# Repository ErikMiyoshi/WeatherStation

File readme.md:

# 💡 Multi-Domain Learning Project: Hardware, Firmware & Software

Welcome to this project that combines **hardware design**, **embedded firmware**, and **application-level software**. The project is a portable weather station that gets temperature, humidity, pressure and show on a dashboard.

## 🧭 Project Goal

This is a personal project for me to learning all aspects of an embedded system project that involves:

- 🔧 **Hardware**: Circuit design, schematics, and PCB development
- 🧠 **Firmware**: Embedded code for microcontrollers, in this case ESP32
- 💻 **Software**: Applications that interact with the device, including dashboards and data logging

The objective is to **understand how these layers connect**, and how to manage a multidisciplinary project effectively.

---

## 🗂 Repository Structure

WeatherStation/
├── HW/ # Schematics, PCB design files (KiCad, etc.)
├── FW/ # Embedded C/C++ code (e.g., ESP-IDF)
├── SW/ # Python, Flask, GUI application (e.g., dashboard)
├── docs/ # Documentation, diagrams, and learning notes
├── LICENSE
└── README.md

---

## 📌 What I'm learning

- Designing a hardware system using open-source tools
- Writing low-level embedded firmware to read sensors and communicate
- Creating software tools to visualize and log the collected data
- Managing a complete project in a clean and modular way

---

## 🛠 Tech Stack

| Layer      | Technology                        |
|------------|-----------------------------------|
| Hardware   | KiCad, breadboards, ESP32, sensors|
| Firmware   | C, C++, ESP-IDF, MQTT             |
| Software   | Python, Flask, MQTT, Chart.js     |
| Tools      | Git, VSCode, KiCad, esp-idf       |

---

## 🤝 Contributing

This is a learning project. Contributions are welcome! Feel free to open issues, suggest improvements, or ask questions. The goal is to learn collaboratively.

I'm not the best at programming and this project is also for me to improve my ability in writing code.

## 📄 License

This project is licensed under the MIT License. See LICENSE for details.

## 🙋‍♂️ Author
Created by Erik as a personal journey to explore full-stack embedded systems.

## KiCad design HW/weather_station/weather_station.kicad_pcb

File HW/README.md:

# 🔧 Hardware Design for WeatherStation Project

This folder contains all the hardware-related files and documentation for the project focused on designing and building the physical electronic system.

## 🎯 Purpose

The hardware part of this project aims to develop the board that will be used:

- Basic circuit design principles
- Sensor interfacing and connections
- PCB design and layout using open-source tools
- Integration with embedded firmware on microcontrollers

---

## 📚 Learning Resources

- Basic electronics and circuit theory  
- How to read and create schematics  
- PCB design best practices  
- Hardware debugging tips

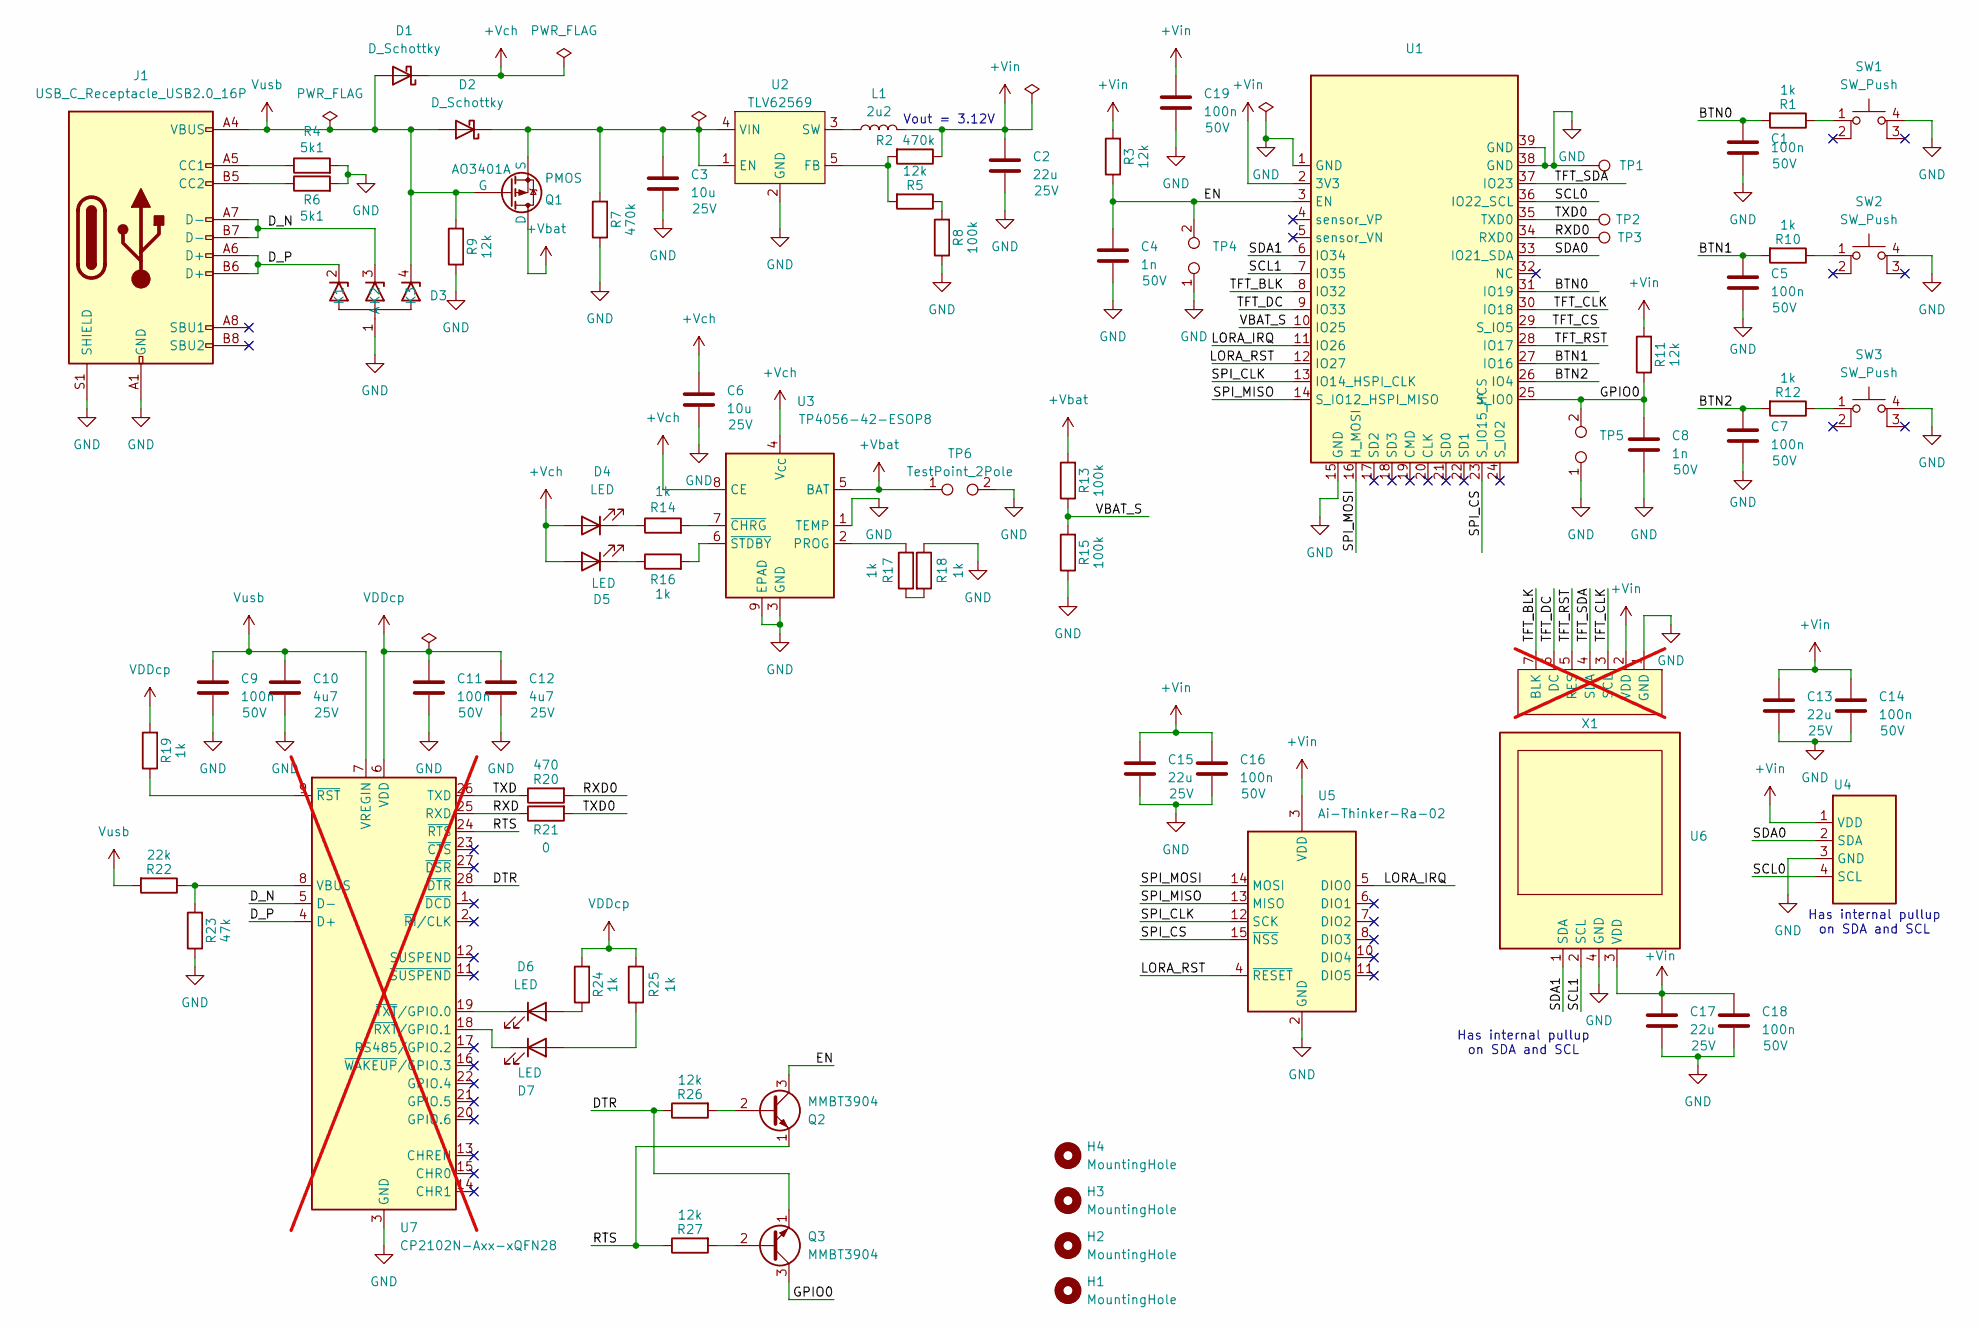
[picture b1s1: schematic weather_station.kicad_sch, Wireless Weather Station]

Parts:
C1, C5, C7, C9, C11, C14, C16, C18, C19: 100n; C_0603_1608Metric; Voltage 50V; LCSC Part # C14663
C2, C13, C15, C17: 22u; C_0805_2012Metric; Voltage 25V; LCSC Part # C45783
C3, C6: 10u; C_0805_2012Metric; Voltage 25V; LCSC Part # C15850
C4, C8: 1n; C_0603_1608Metric; Voltage 50V; LCSC Part # C1588
C10, C12: 4u7; C_0805_2012Metric; Voltage 25V; LCSC Part # C1779
D1, D2: D_Schottky; D_SMA; LCSC Part # C2480
D3: SOT-143; LCSC Part # C3040626
D4, D5, D6, D7: LED; LED_0603_1608Metric; LCSC Part # C2286
H1, H2, H3, H4: MountingHole; mounting_hole_2
J1: USB_C_Receptacle_USB2.0_16P; USB_C_Receptacle_GCT_USB4105-xx-A_16P_TopMnt_Horizontal_fix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; LCSC Part # C2765186
L1: 2u2; Inductor_4.5x4.1x2; LCSC Part # C22463806
Q1: PMOS; SOT-23_(pins_inverted); LCSC Part # C15127
Q2, Q3: MMBT3904; SOT-23_(pins_12_inverted); LCSC Part # C20526
R1, R10, R12, R14, R16, R17, R18, R19, R24, R25: 1k; R_0603_1608Metric_Pad0.98x0.95mm_HandSolder; LCSC Part # C21190
R2, R7: 470k; R_0603_1608Metric_Pad0.98x0.95mm_HandSolder; LCSC Part # C23178
R3, R5, R9, R11, R26, R27: 12k; R_0603_1608Metric_Pad0.98x0.95mm_HandSolder; LCSC Part # C22790
R4, R6: 5k1; R_0603_1608Metric_Pad0.98x0.95mm_HandSolder; LCSC Part # C23186
R8, R13, R15: 100k; R_0603_1608Metric_Pad0.98x0.95mm_HandSolder; LCSC Part # C25803
R20: 470; R_0603_1608Metric_Pad0.98x0.95mm_HandSolder; LCSC Part # C23179
R21: 0; R_0603_1608Metric_Pad0.98x0.95mm_HandSolder; LCSC Part # C21189
R22: 22k; R_0603_1608Metric_Pad0.98x0.95mm_HandSolder; LCSC Part # C31850
R23: 47k; R_0603_1608Metric_Pad0.98x0.95mm_HandSolder; LCSC Part # C25819
SW1, SW2, SW3: SW_Push; tactile_switch_6x6; LCSC Part # C455110
TP1, TP2, TP3: TestPoint; TestPoint_THTPad_1.5x1.5mm_Drill0.7mm
TP4, TP5: TestPoint_2Pole; PinHeader_1x02_P2.54mm_Vertical
TP6: TestPoint_2Pole; TestPoint_2Pads_Pitch5.08mm_Drill1.3mm
U1: ESP32-WROOM-32 or ESP32S_no_paste
U2: TLV62569; SOT-23-5; LCSC Part # C141836
U3: TP4056-42-ESOP8; SOIC-8-1EP_3.9x4.9mm_P1.27mm_EP2.41x3.3mm_ThermalVias_via_0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; LCSC Part # C725790
U4: BMP280_AHT20
U5: Ai-Thinker-Ra-02; Ai-Thinker-Ra-01-LoRa_no_paste
U6: 0.96inch_lcd
U7: CP2102N-Axx-xQFN28; QFN-28-1EP_5x5mm_P0.5mm_EP2.7x2.7mm_ThermalVias_via_0.3mm; not fitted
X1: Header_7x2.54_smt; not fitted

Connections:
+Vbat: Q1.1 (D), R13.2, TP6.1, U3.5 (BAT)
+Vch: C6.1, D1.1 (K), D4.2 (A), D5.2 (A), U3.4 (V_{CC}), U3.8 (CE)
+Vin: C2.1, C13.1, C14.1, C15.1, C16.1, C17.1, C18.1, C19.1, L1.2, R2.1, R3.2, R11.2, U1.2 (3V3), U4.1 (VDD), U5.3 (VDD), U6.3 (VDD), X1.2 (VDD)
/BTN0: C1.1, R1.2, U1.31 (IO19)
/BTN1: C5.1, R10.2, U1.27 (IO16)
/BTN2: C7.1, R12.2, U1.26 (IO4)
/DTR: Q3.1 (E), R26.1, U7.28 (~DTR)
/D_N: D3.3 (K2), J1.A7 (D-), J1.B7 (D-), U7.5 (D-)
/D_P: D3.2 (K1), J1.A6 (D+), J1.B6 (D+), U7.4 (D+)
/EN: C4.1, Q2.3 (C), R3.1, TP4.2, U1.3 (EN)
/GPIO0: C8.1, Q3.3 (C), R11.1, TP5.2, U1.25 (S_IO0)
/LORA_IRQ: U1.11 (IO26), U5.5 (DIO0)
/LORA_RST: U1.12 (IO27), U5.4 (~RESET)
/RTS: Q2.1 (E), R27.1, U7.24 (~RTS)
/RXD: R21.1, U7.25 (RXD)
/RXD0: R20.2, TP3.1, U1.34 (RXD0)
/SCL0: U1.36 (IO22_SCL), U4.4 (SCL)
/SCL1: U1.7 (IO35), U6.2 (SCL)
/SDA0: U1.33 (IO21_SDA), U4.2 (SDA)
/SDA1: U1.6 (IO34), U6.1 (SDA)
/SPI_CLK: U1.13 (IO14_HSPI_CLK), U5.12 (SCK)
/SPI_CS: U1.23 (S_IO15_HCS), U5.15 (~NSS)
/SPI_MISO: U1.14 (S_IO12_HSPI_MISO), U5.13 (MISO)
/SPI_MOSI: U1.16 (H_MOSI), U5.14 (MOSI)
/TFT_BLK: U1.8 (IO32), X1.7 (BLK)
/TFT_CLK: U1.30 (IO18), X1.3 (SCL)
/TFT_CS: U1.29 (S_IO5)
/TFT_DC: U1.9 (IO33), X1.6 (DC)
/TFT_RST: U1.28 (IO17), X1.5 (RES)
/TFT_SDA: U1.37 (IO23), X1.4 (SDA)
/TXD: R20.1, U7.26 (TXD)
/TXD0: R21.2, TP2.1, U1.35 (TXD0)
/VBAT_S: R13.1, R15.2, U1.10 (IO25)
GND: C1.2, C2.2, C3.2, C4.2, C5.2, C6.2, C7.2, C8.2, C9.2, C10.2, C11.2, C12.2, C13.2, C14.2, C15.2, C16.2, C17.2, C18.2, C19.2, D3.1 (A), J1.A1 (GND), J1.A12 (GND), J1.B1 (GND), J1.B12 (GND), J1.S1 (SHIELD), R4.2, R6.2, R7.1, R8.1, R9.1, R15.1, R18.1, R23.1, SW1.4 (A), SW2.4 (A), SW3.4 (A), TP1.1, TP4.1, TP5.1, TP6.2, U1.1 (GND), U1.15 (GND), U1.38 (GND), U1.39 (GND), U2.2 (GND), U3.1 (TEMP), U3.3 (GND), U3.9 (EPAD), U4.3 (GND), U5.1 (GND), U5.2 (GND), U5.9 (GND), U5.16 (GND), U6.4 (GND), U7.3 (GND), U7.29 (GND), X1.1 (GND)
unnamed: C3.1, D2.1 (K), Q1.3 (S), R7.2, U2.1 (EN), U2.4 (VIN)
unnamed: D4.1 (K), R14.1
unnamed: D5.1 (K), R16.1
unnamed: D6.2 (A), R24.1
unnamed: D6.1 (K), U7.19 (~TXT/GPIO.0)
unnamed: D7.2 (A), R25.2
unnamed: D7.1 (K), U7.18 (~RXT/GPIO.1)
unnamed: J1.A5 (CC1), R4.1
unnamed: J1.B5 (CC2), R6.1
unnamed: Q2.2 (B), R26.2
unnamed: Q3.2 (B), R27.2
unnamed: R1.1, SW1.1
unnamed: R5.1, R8.2
unnamed: R10.1, SW2.1
unnamed: R12.1, SW3.1
unnamed: R17.1, R18.2
unnamed: R2.2, R5.2, U2.5 (FB)
unnamed: L1.1, U2.3 (SW)
unnamed: R17.2, U3.2 (PROG)
unnamed: R14.2, U3.7 (~CHRG)
unnamed: R16.2, U3.6 (~STDBY)
unnamed: R22.1, R23.2, U7.8 (VBUS)
unnamed: R19.1, U7.9 (~RST)
VDDcp: C11.1, C12.1, R19.2, R24.2, R25.1, U7.6 (VDD)
Vusb: C9.1, C10.1, D1.2 (A), D2.2 (A), D3.4 (K3), J1.A4 (VBUS), J1.A9 (VBUS), J1.B4 (VBUS), J1.B9 (VBUS), Q1.2 (G), R9.2, R22.2, U7.7 (VREGIN)

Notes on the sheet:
Has internal pullup on SDA and SCL
Vout = 3.12V

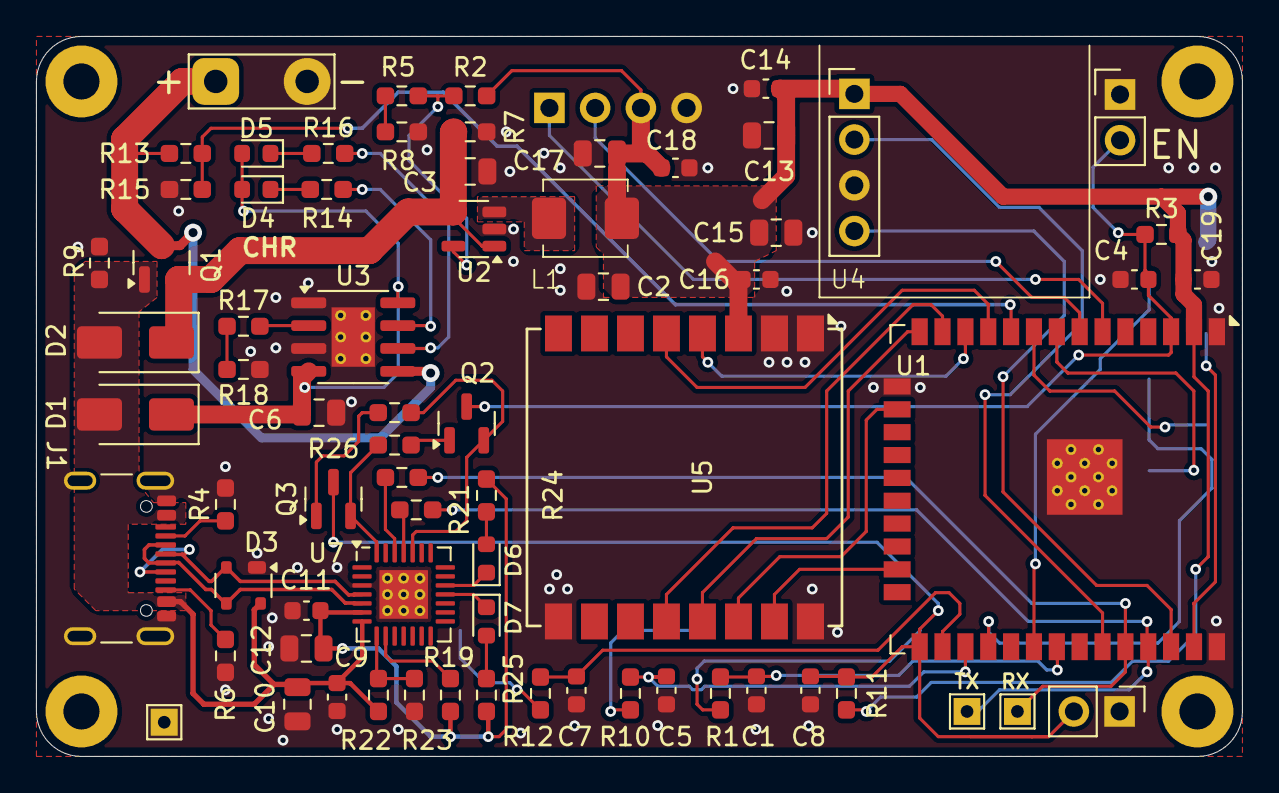
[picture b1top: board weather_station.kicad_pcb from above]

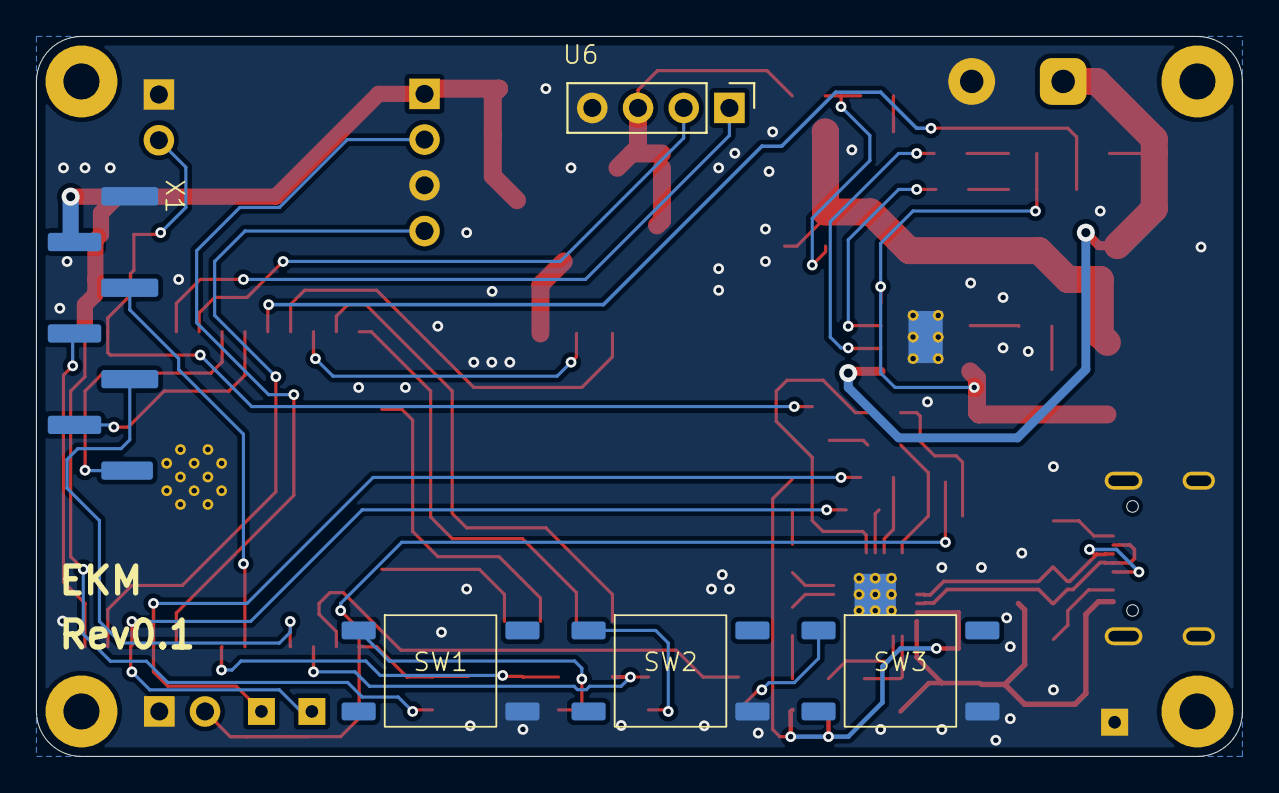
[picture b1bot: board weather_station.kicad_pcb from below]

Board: 2 copper layers, 67.0 x 40.0 mm, 79 parts (5 on the bottom side), 58 nets.

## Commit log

2025-04-03 Initial circuit - USBC, CP2102, ESP32
2025-04-04 Schematic done, Layout in progress
2025-04-06 Adjusting components
2025-04-07 Adjust min via hole size to 0.3mm
2025-04-08 Revision for production
2025-06-08 Adjusting folders and separate firmware and hardware
2025-06-08 Creating idf project for firmware
2025-06-09 add functions to connect to wifi
2025-06-09 add functions to read aht20 sensor
2025-06-14 add functions to read bmp280
2025-06-15 add basic functions for using oled display
2025-06-15 add a queue and monitor to share data between sensors and display
2025-06-15 add sntp
2025-06-16 add a basic menu to display on oled screen, using a joystick hw-504 to select options (for tests only, in future will be used 3 push buttons)
2025-07-08 Add battery voltage monitor
2025-07-12 turn off oled display after some time if not used
2025-07-19 Update Readme and add license
2025-07-19 Add readme for hardware
2025-07-20 Add mqtt to project
2025-07-20 basic mqtt server with paho-mqtt and integration with mysql (mariadb)
2025-07-20 Simple backend file in flask to expose data from database
2025-07-20 Initial tests with charts.js
2025-07-26 Add nvs code to store a variable to indicate if a device is battery operated
2025-07-26 Change ADC to one shot, disable display, enable deepsleep
2025-07-26 Add options to select which sensor will be shown on chart
2025-07-27 Disabling temporarily lvgl and dislplay as it was breaking the code
2025-08-14 Fix code to send battery voltage only one time
2025-08-31 Start a frontend project with vue+tailwindcss
2025-09-20 Basic dashboard with vue
2025-09-21 Initial dashboard with only html, css and js
2026-01-19 Backup files, may be usefull or not
2026-03-22 Generating pdf files for hw
